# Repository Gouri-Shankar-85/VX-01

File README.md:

# VX-01 Multi-Terrain Robot

A modular multi-terrain robotic platform combining the agility of a hexapod crawler with the aerial capabilities of a multirotor drone. The system is designed for autonomous and manual navigation across land and air, powered by a distributed compute architecture using ROS 2 and ArduPilot.

---

## 🌟 Key Features

- **Hexapod Locomotion:** Real-time 18-DOF inverse kinematics (IK) executing synchronized Tripod and Wave gaits.
- **Aerial Flight:** Fully integrated drone flight (STABILIZE, GUIDED, AUTO) utilizing a MAVROS bridge.
- **Hybrid Mode Management:** Safe state machine transitioning the robot from ground crawling to aerodynamic flight postures.
- **Visual SLAM & Odometry:** RTAB-Map integration using depth camera data for 3D point cloud generation and obstacle avoidance.
- **Computer Vision:** Real-time object detection, victim identification, and terrain walkability classification using YOLOv4-tiny.
- **Mission Control Dashboard:** A sleek, React-based web UI communicating over `rosbridge_server` for live telemetry, manual teleop, and mapping visualization.

---

## 🛠️ Hardware Stack

| Component | Description |
|-----------|-------------|
| **RDK X5 (ARM64)** | High-level compute board running Ubuntu 22.04 + ROS 2 Humble (Dockerized). Handles IK, SLAM, Vision, and the Web Dashboard. |
| **Radiolink PIX6 (ArduPilot)** | Flight controller connected via USB (MAVLink). Manages aerial stabilization, IMU processing, and GPS. |
| **Pololu Maestro Mini** | Dedicated serial servo controller actuating the 18 high-torque hexapod leg servos. |
| **YDLIDAR HP60C RGBD** | Depth Camera mounted on the front chassis for perception and mapping. |
| **Benewake TFmini-S** | Downward-facing LiDAR distance sensor for precise altitude holding. |
| **Hiwonder IM10A** | External IMU for redundant odometry. |

---

## 📦 Workspace Architecture

The software is strictly modularized into distinct ROS 2 packages within the `vx01_ws/src` directory:

```
vx01_ws/src
├── vx01_bringup          # Master hardware/sim launch files and QoS relays
├── vx01_camera           # Driver for the YDLIDAR depth camera
├── vx01_control          # Locomotion meta-package (Aerial, Aquatic, Hexapod IK, Mode Manager)
├── vx01_description      # Robot URDF, Xacro kinematics, and STL 3D meshes
├── vx01_hardware         # ros2_control interfaces for the Pololu Maestro and Drone GPIOs
├── vx01_imu              # External I2C/Serial IMU drivers
├── vx01_mapping          # RTAB-Map visual SLAM integration
├── vx01_mavros_bridge    # C++ nodes bridging ArduPilot/MAVROS telemetry to custom topics
├── vx01_msgs             # Custom ROS 2 interfaces (DroneState, HexapodState, Thrust)
├── vx01_perception       # OpenCV + YOLOv4-tiny stack for victim and terrain detection
└── vx01_simulation       # Gazebo SITL physics environments
```
*(Refer to the individual `README.md` inside each package for detailed node, topic, and build instructions.)*

---

## 🚀 Quick Start Guide

This project is fully containerized. Please refer to the [VX01 Docker & Deployment Manual](VX01_Docker_Manual.md) in the root directory for complete, in-depth documentation.

### 1. Simulation on Laptop
Run the simulation stack (Gazebo + ROS 2 Bridge + Dashboard) on your computer without needing the physical hardware:

```bash
cd ~/vx-01
# Start the simulation profile containers in the background
docker compose --profile sim up -d

# Open the Gazebo simulation window from inside the container
docker exec -it vx01-sim bash
ros2 launch vx01_simulation sim.launch.py
```
Open a browser and go to `http://localhost:5173` to control the simulated robot!

### 2. Daily Code Development
To edit code and test it without affecting the real robot:

```bash
cd ~/vx-01
# Start the development container
docker compose --profile dev up -d
docker exec -it vx01-dev bash

# Once inside the container, build the workspace:
cd /vx01_ws
colcon build --symlink-install
source install/setup.bash
```
*Note: Your `~/vx-01/vx01_ws/src/` folder is mounted live into the container. Any code changes you make on your laptop instantly appear inside!*

### 3. Deploying to Real Hardware (RDK X5 / Raspberry Pi)
To update the physical robot with your latest code:

```bash
# On your laptop, trigger the ARM64 cloud build:
./build.sh build-arm-ci
# (Wait for the GitHub Action to finish building the image)

# SSH into your robot and pull the latest image:
docker pull gourishankar85/vx01-base:humble-arm64
docker compose -f ~/vx01/docker-compose.rdk.yml down
docker compose -f ~/vx01/docker-compose.rdk.yml up -d
```

### Accessing the Dashboard
Whenever the `sim` or hardware containers are running, you can access the Mission Control Dashboard:
- **Locally (Simulation):** `http://localhost:5173`
- **Real Robot:** `http://<ROBOT_IP>:5173`

---

## 🤝 Contributing
Pull requests are welcome. When adding new ROS 2 nodes, ensure they are properly integrated into the `vx01_bringup` launch files and that relevant `ros2_control` hardware parameters are updated.

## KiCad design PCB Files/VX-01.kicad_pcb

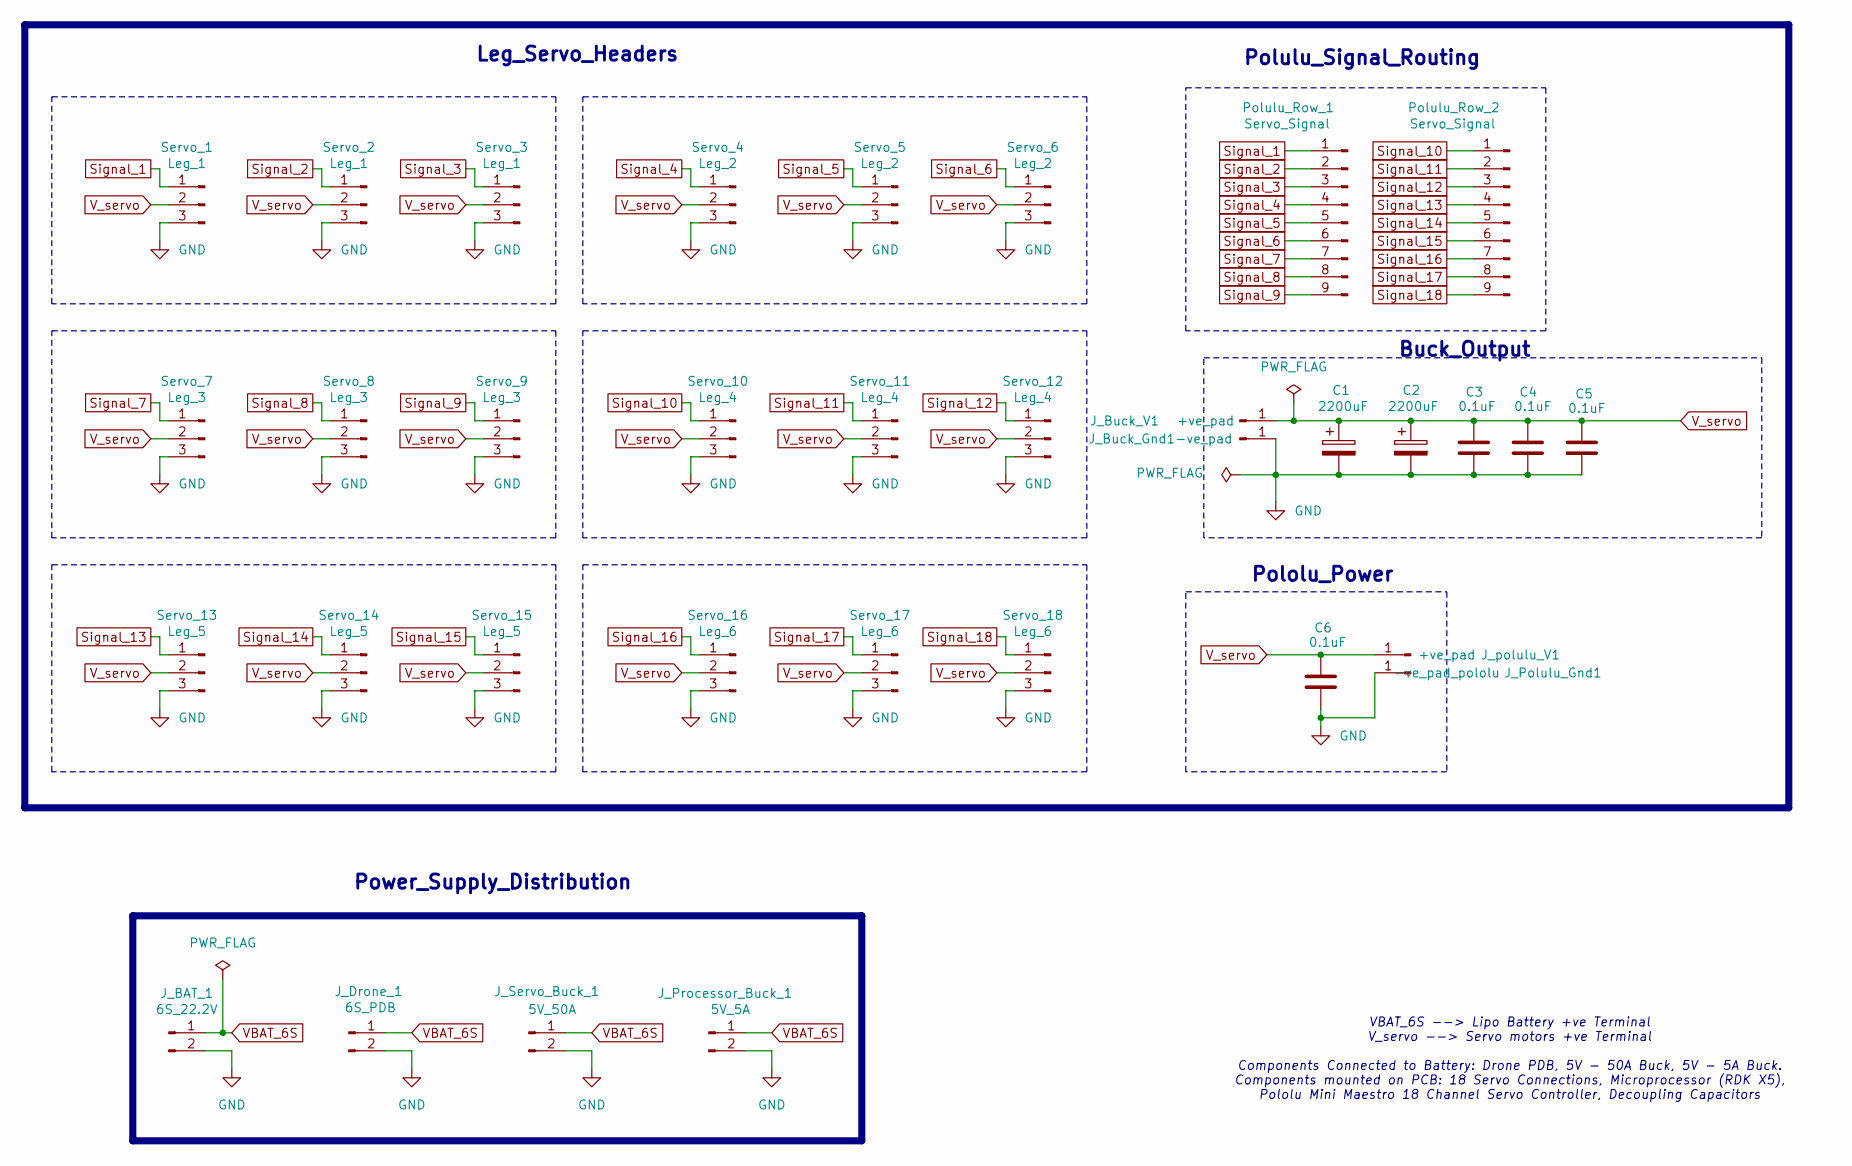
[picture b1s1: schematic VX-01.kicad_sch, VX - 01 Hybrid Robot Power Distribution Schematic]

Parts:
C1, C2: 2200uF; C_Radial_D12.5mm_H25.0mm_P5.00mm
C3, C4, C5, C6: 0.1uF; C_0805_2012Metric_Pad1.18x1.45mm_HandSolder
J_BAT_1: 6S_22.2V; XT-90F
J_Buck_Gnd1: -ve_pad; SolderWirePad_1x01_SMD_5x10mm
J_Buck_V1: +ve_pad; SolderWirePad_1x01_SMD_5x10mm
J_Drone_1: 6S_PDB; XT-90F
J_Polulu_Gnd1: -ve_pad_pololu; SolderWirePad_1x01_SMD_5x10mm
J_Processor_Buck_1: 5V_5A; AMASS_XT60-F_1x02_P7.20mm_Vertical
J_Servo_Buck_1: 5V_50A; AMASS_XT60-F_1x02_P7.20mm_Vertical
J_polulu_V1: +ve_pad; SolderWirePad_1x01_SMD_5x10mm
Polulu_Row_1, Polulu_Row_2: Servo_Signal; PinHeader_1x09_P2.54mm_Vertical
Servo_1, Servo_2, Servo_3: Leg_1; PinHeader_1x03_P2.54mm_Vertical
Servo_4, Servo_5, Servo_6: Leg_2; PinHeader_1x03_P2.54mm_Vertical
Servo_7, Servo_8, Servo_9: Leg_3; PinHeader_1x03_P2.54mm_Vertical
Servo_10, Servo_11, Servo_12: Leg_4; PinHeader_1x03_P2.54mm_Vertical
Servo_13, Servo_14, Servo_15: Leg_5; PinHeader_1x03_P2.54mm_Vertical
Servo_16, Servo_17, Servo_18: Leg_6; PinHeader_1x03_P2.54mm_Vertical

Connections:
GND: C1.2, C2.2, C3.2, C4.2, C5.2, C6.2, J_BAT_1.2, J_Buck_Gnd1.1, J_Drone_1.2, J_Polulu_Gnd1.1, J_Processor_Buck_1.2, J_Servo_Buck_1.2, Servo_1.3, Servo_2.3, Servo_3.3, Servo_4.3, Servo_5.3, Servo_6.3, Servo_7.3, Servo_8.3, Servo_9.3, Servo_10.3, Servo_11.3, Servo_12.3, Servo_13.3, Servo_14.3, Servo_15.3, Servo_16.3, Servo_17.3, Servo_18.3
Signal_1: Polulu_Row_1.1, Servo_1.1
Signal_2: Polulu_Row_1.2, Servo_2.1
Signal_3: Polulu_Row_1.3, Servo_3.1
Signal_4: Polulu_Row_1.4, Servo_4.1
Signal_5: Polulu_Row_1.5, Servo_5.1
Signal_6: Polulu_Row_1.6, Servo_6.1
Signal_7: Polulu_Row_1.7, Servo_7.1
Signal_8: Polulu_Row_1.8, Servo_8.1
Signal_9: Polulu_Row_1.9, Servo_9.1
Signal_10: Polulu_Row_2.1, Servo_10.1
Signal_11: Polulu_Row_2.2, Servo_11.1
Signal_12: Polulu_Row_2.3, Servo_12.1
Signal_13: Polulu_Row_2.4, Servo_13.1
Signal_14: Polulu_Row_2.5, Servo_14.1
Signal_15: Polulu_Row_2.6, Servo_15.1
Signal_16: Polulu_Row_2.7, Servo_16.1
Signal_17: Polulu_Row_2.8, Servo_17.1
Signal_18: Polulu_Row_2.9, Servo_18.1
VBAT_6S: J_BAT_1.1, J_Drone_1.1, J_Processor_Buck_1.1, J_Servo_Buck_1.1
V_servo: C1.1, C2.1, C3.1, C4.1, C5.1, C6.1, J_Buck_V1.1, J_polulu_V1.1, Servo_1.2, Servo_2.2, Servo_3.2, Servo_4.2, Servo_5.2, Servo_6.2, Servo_7.2, Servo_8.2, Servo_9.2, Servo_10.2, Servo_11.2, Servo_12.2, Servo_13.2, Servo_14.2, Servo_15.2, Servo_16.2, Servo_17.2, Servo_18.2

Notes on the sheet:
Leg_Servo_Headers
Pololu_Power
Polulu_Signal_Routing
Buck_Output
VBAT_6S --> Lipo Battery +ve Terminal V_servo --> Servo motors +ve Terminal Components Connected to Battery: Drone PDB, 5V - 50A Buck, 5V - 5A Buck. Components mounted on PCB: 18 Servo Connections, Microprocessor (RDK X5), Pololu Mini Maestro 18 Channel Servo Controller, Decoupling Capacitors
Power_Supply_Distribution

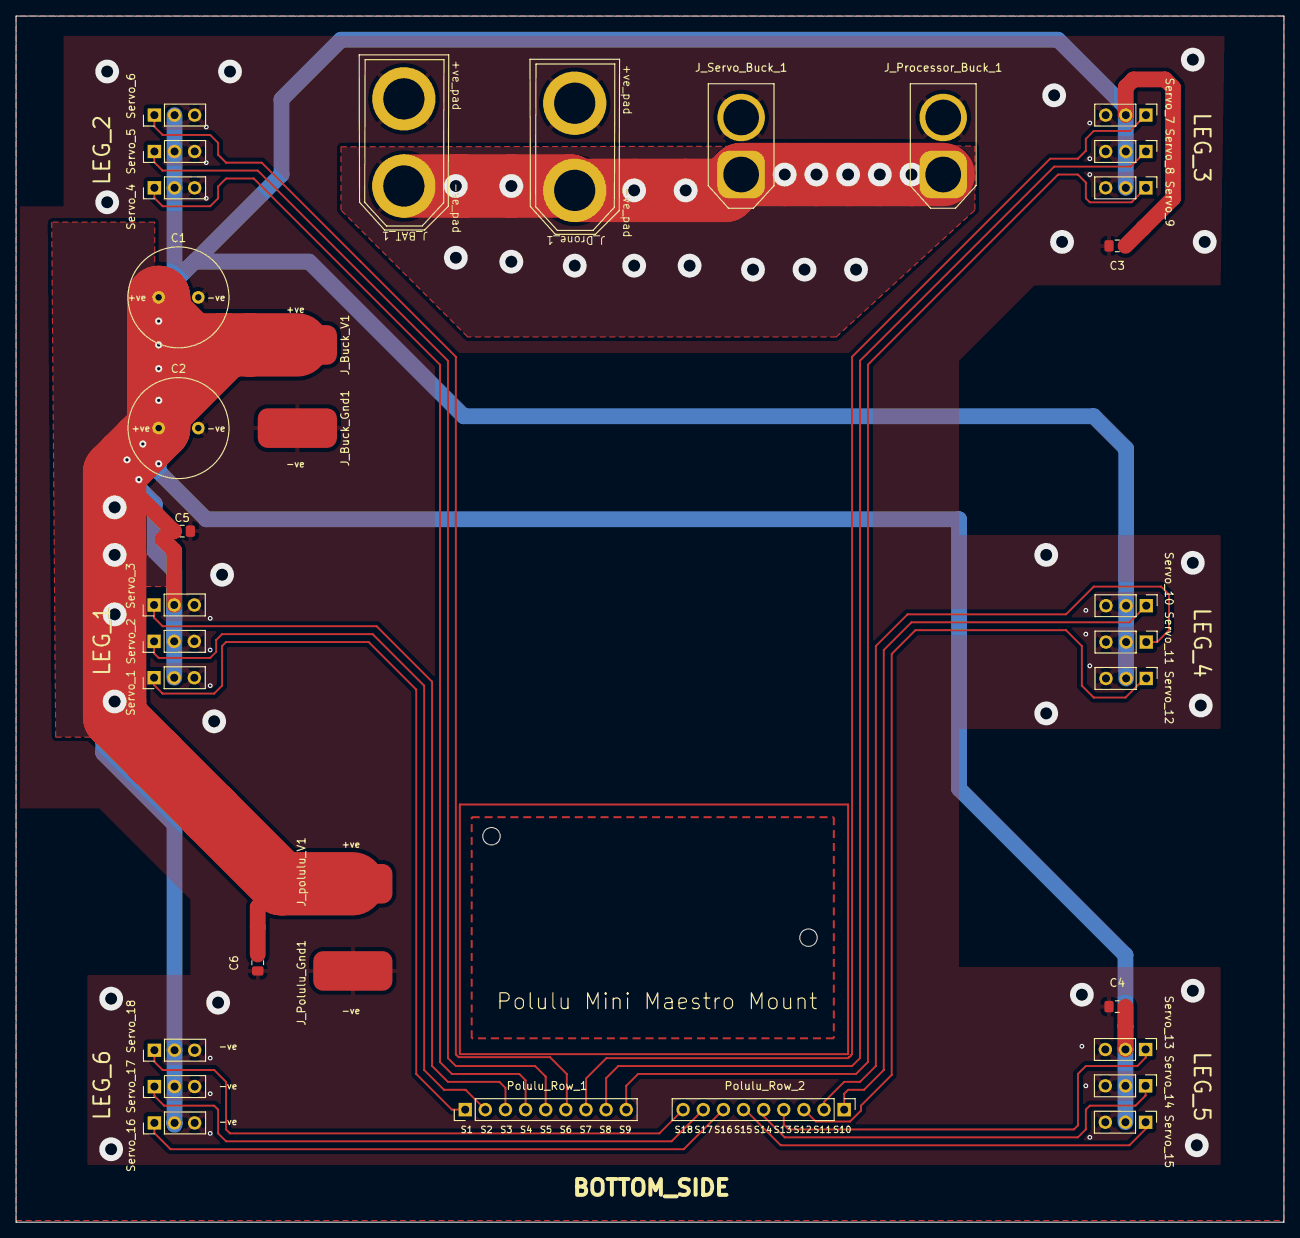
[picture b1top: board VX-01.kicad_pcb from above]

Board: 2 copper layers, 160.0 x 152.2 mm, 34 parts (0 on the bottom side), 21 nets.

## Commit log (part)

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2026-02-26 lib updated
2026-02-26 bezeir curve fixed
2026-02-26 locomotion updated
2026-02-26 to tibi
2026-02-26 hexapod walk node
2026-02-27 walk node updated
2026-03-06 camera sdk removed
2026-03-06 demo removed
2026-03-07 fix: hexapod joint limits changed
2026-03-07 walk goal script
2026-03-07 locomotion parameters
2026-03-08 feat(locomotion): add ROS2 node with tripod gait, IK-based walking, and standby pose sequencing
2026-03-08 fix: home_z set to stay within tibia limit
2026-03-08 fix(locomotion): slow step_period and add use_sim_time to unblock joint execution in Gazebo
2026-03-08 fix(locomotion): remove velocity scaling so open-loop gait actually translates feet
2026-03-08 test(ik): theta_3 sign chnaged
2026-03-08 fix: Bezier swing arc + full drag sweep for all 6 legs
2026-03-08 fix: projects the stride onto each leg's local frame using the mounting angle alpha
2026-03-08 fix(description(: initial pose for hexapod sim changed
2026-03-08 fix(locomotion): correct forward walk IK by reducing home_x and fixing body_radius double-count in updateLeg
2026-03-08 test: gait_x value passed to ik_x
2026-03-08 test: local_y changed to cos to fix the sideways walk
2026-03-08 test: ik_y changed to have a leg frame calculation
2026-03-08 fix(gait): remove duplicate global_t declaration in drag phase
2026-03-08 feat(body): add BodyKinematics and BodyTranslation modules; wire updateLeg through O-frame transform per reference
2026-03-08 fix(locomotion): pass (home_x - body_radius) as O-frame body_x into bodyToLegFrame to fix diagonal leg IK failures
2026-03-08 fix(config): reduce step_length to 50 to fit diagonal leg IK reach with home_x=222.8
2026-03-08 locomotion fixed
2026-03-09 home_x changed
2026-03-09 fix: add home_z offset to gait_z in updateLeg
2026-03-09 fix: reduce home_x and step_length to eliminate stretched leg posture
2026-03-09 test:theta_3 sig reverted back
2026-03-09 fix: tune yaml for IK reachability
2026-03-09 fix: project stride offset into leg-local frame in updateLeg, tune yaml for IK reachability
2026-03-10 feat(vx01_msgs): add 8 custom msg types for victim detection, terrain, mission, and robot status
2026-03-10 fix:mount the workspace into the container.
2026-03-11 add(perception): perception nodes - victim detector, terrain classifier and mission nodes
2026-03-13 fix: hexapod hw controller and launch file update
2026-03-13 Ignore core dumps and vx01_camera
2026-03-13 local changes before pull
2026-03-13 fix(launch): correct parameter order and types in hw launch file
2026-03-13 fix(urdf): pass serial_port and baud_rate as xacro args instead of hardcoding
2026-03-13 update : servo mapping coxa reversed
2026-03-14 feat(servo): add software interpolation for smooth joint motion
2026-03-14 fix(locomotion): correct IK femur sign, fix JTC flooding, fix gait block-rate sending
2026-03-14 fix: locomotion parameters updated
2026-03-14 fix: restore single-point sendLegTrajectory overload for standby pose, suppress unused S warning
2026-03-14 fix: correct tripod gait to true 50/50 duty cycle, remove all-stance block 5
2026-03-19 fix: correct tripod stride direction, separate swing/stance trajectory dispatch
2026-03-19 fix: use full bezier bx/by/bz for swing, scale*T/2 for drag Y
2026-03-19 fix: ik 'r2' eqn corrected
2026-03-20 fix: validateWorkspace use Y-sweep check; increase step_height for visible lift
2026-03-20 fix(locomotion): tripod gait sync, drag leg hold, and stride length
2026-03-21 fix: fire trajectories only at group-start blocks 0/3; full 3-block swing+drag per trigger
2026-03-21 fix: separate swing/drag send loops to prevent mid-motion interruption; step_height=70
2026-03-21 update: femur standy pose to -1.2
2026-03-21 fix: decouple theta1 coxa sweep from theta2/theta3 Z lift in sampleSwingAtGlobalT
2026-03-21 fix: use stance_femur/tibia directly in swing; no IK coupling; femur lifts correctly
2026-03-22 feat: add turn-in-place node with CCW/CW direction param
2026-03-22 fix: hexapod_fw_walk_node updated with correct lib name
2026-03-22 fix: add __main__ guard to victim_detector_node
2026-03-22 fix: explicit bool casts and NaN guard in terrain_classifier_node
2026-03-22 fix: remove viz, add static TF
2026-03-22 feat: lifecycle walk/turn nodes with autonomous victim approach node
2026-03-23 docker: dockerfile base libuvc to uvc
2026-03-23 updated dockerfile base
2026-03-23 build.sh updted to try 3 times to build he image
2026-03-24 git commit -m "fix: dynamic rosbridge URL from window.location, fix dockerignore"
2026-03-24 regenerate package-lock.json with roslib and socket.io deps
2026-03-24 fix(vx01_msgs): add rosidl runtime export for proper package discovery
2026-03-25 locomotion: fixed for standalone testing of hexapod
2026-03-25 revert(locomotion): remove lifecycle nodes, restore original plain Node walk/turn
2026-03-25 update: removed gpio group from dockerfile.base
2026-03-26 fix: added a use sim time argument to forward walk launch file
2026-03-26 test: increased the step height and step length
2026-03-26 locmotion: cmakelist updated
2026-03-26 Fix gait_config.yaml: correct leg_joint_names format to map (0-5 keys)
2026-03-27 fix(locomotion): derive home pose from xacro FK and raise controller trajectory tolerance
2026-04-05 feat: add vx01_msgs dependency to package.xml
2026-04-05 feat: enhance dashboard with real-time telemetry, robot status monitoring, and expanded manual control capabilities
2026-04-05 feat: implement ArduPilot SITL integration, hybrid mode manager, and aerial controller nodes
2026-04-05 feat: enable IMU and sensor plugins with ogre2 render engine in empty_world.sdf
2026-04-05 fix: update IMU topic configuration and sensor name reference for Gazebo bridge compatibility
2026-04-05 fix: update MAVProxy and MAVROS connection protocol from TCP to UDP for improved telemetry stability
2026-04-05 refactor: update ArduPilot simulation arguments and switch MAVROS connection to TCP port 5760
2026-04-05 feat: enable use_sim_time in mavros launch parameters
2026-04-05 feat: add velocity command and state interfaces for four propeller joints to ros2_control configuration
2026-04-05 feat: initialize backend node_modules and update robot URDF configuration
2026-04-05 feat: integrate RTAB-Map for SLAM and update simulation launch configurations to support use_sim_time
2026-04-05 feat: add MAVROS drone control support, telemetry stream configuration, and force-arming capabilities
2026-04-05 feat: add ArduPilot simulation bypass parameters, implement cycle-based trajectory synchronization in locomotion, and tune RTAB-Map simulation settings.
2026-04-05 refactor: optimize RTAB-Map odometry parameters and update force-arm sequence to STABILIZE mode for improved reliability
2026-04-06 refactor: optimize IK calculations and adjust gait parameters for improved workspace stability
2026-04-06 fix: replace invalid --out argument with --serial0 for ArduPilot SITL MAVLink output
2026-04-08 refactor: switch MAVROS connection from TCP to UDP for improved simulation stability
2026-04-08 refactor: implement leg-to-body frame transformations, update gait parameters for tripod stability, and correct ArduPilot plugin configuration.
2026-04-08 feat: add rosbridge_server to launch configuration and fix ArduPilotPlugin library path in URDF
2026-04-08 chore: update ArduPilot serial port to 14551 and simplify MAVROS fcu_url configuration
2026-04-08 fix: update MAVROS fcu_url configuration and remove redundant comments in hybrid simulation launch file
2026-04-08 fix: swap MAVROS fcu_url ports to correct UDP communication direction
2026-04-08 chore: update ArduPilot SITL model and switch MAVROS connection to TCP
2026-04-08 feat: load ArduPilot default parameters and remove redundant MAVROS frame configuration services
2026-04-08 feat: add additional periodic arming attempts to hybrid simulation launch file
2026-04-08 refactor: update drone control to use TwistStamped messages and clean up UI logging and labels
2026-04-08 feat: add ardupilot_sim_bypass.param to SITL launch configuration
2026-04-09 fix: update ROS message type and include header timestamps in takeoff command velocity publisher
2026-04-09 feat: enable use_sim_time for aerial_controller node in hybrid simulation launch
2026-04-09 fix: update ArduPilotPlugin name to match library expectations
2026-04-21 refactor: update hexapod kinematics, gait trajectory interpolation, and default configuration parameters while adding a walk test script.
2026-04-21 refactor: update kinematics, gait parameters, and add Bézier trajectory support for improved locomotion stability
2026-04-21 refactor: clean up backend logs and remove unused simulation shutdown logic
2026-04-24 refactor: simplify hexapod configuration comments and remove deprecated walk test script
2026-04-24 refactor: replace C++ aerial control node with Python-based implementation using rclpy and MAVROS
2026-04-24 fix: update ArduPilotPlugin namespace to ignition::gazebo::systems
2026-04-24 fix: adjust MAVROS parameter timeouts, reorder ArduPilot launch arguments, and update bypass parameters for simulation stability
2026-04-24 chore: configure ArduPilot RC and motor parameters and increase URDF motor multipliers
2026-04-24 feat: add robotNamespace to multicopter motor model plugins in URDF
2026-04-24 fix: increase motor multiplier values in URDF to correct propulsion output scale
2026-04-24 chore: update base inertia properties and reconfigure propeller servo limits
2026-04-24 chore: adjust simulation spawn height and reset gazebo coordinate transformation parameters
2026-04-24 chore: update propeller controller multiplier and p_gain values in URDF
2026-04-24 chore: update ArduPilot serial parameters and tune motor controller gains in URDF
2026-04-25 feat: enable orientation output in IMU sensor configuration
2026-04-25 refactor: update motor control parameters and streamline flight mode transition to GUIDED for takeoff
2026-04-25 chore: update ArduPilot simulation parameters for rate controller and filtering settings
2026-04-26 chore: normalize arm joint orientations and update ArduPilot PID tuning parameters
2026-04-26 refactor: update friction coefficients in simulation and remove IMU bias noise parameters
2026-04-26 chore: increase p_gain from 0.5 to 5.0 for velocity servos in URDF description
2026-04-26 chore: tune MAVROS connection timeouts and update motor control parameters in URDF
2026-04-27 feat: add teleop launch buttons and manual control toggles to hexapod and drone dashboards
2026-04-27 Fix: Add camera SDK path to LD_LIBRARY_PATH
2026-04-28 Fix: Pin Maestro symlink to Command Port (Interface 0)
2026-04-28 chore: update gait parameters and apply tibia joint offset for high-precision movement
2026-04-28 chore: adjust hexapod gait parameters for improved reachability and stability
2026-04-29 chore: adjust home Z-height, increase stand duration, and apply joint offset corrections to locomotion kinematics
2026-04-29 feat: implement dynamic home coordinate calculation and update locomotion gait parameters
2026-04-29 chore: update hexapod gait parameters and home position for increased stability
2026-04-29 chore: update step_period in hexapod configuration to 2.0 seconds for optimized gait cycle
2026-04-29 chore: update stand-pose joint commands and home position for improved walking IK alignment
2026-05-04 feat: add drone attitude visualization and real-time telemetry metrics to dashboard
2026-05-05 build: add host network driver option to buildx builder creation
2026-05-11 feat: update camera resolution settings, fix hexapod angle calculation, and add MAVROS distance sensor configuration
2026-05-11 Fix typo in hexapod_node.py
2026-05-11 Fix undefined function crash in dashboard and satisfy Pixhawk RC arming checks
2026-05-11 docs: Add hero image to main README
2026-05-12 docs: Generate clean tree-based READMEs matching the original camera documentation format
2026-05-12 docs: Update hardware specs and align quickstart instructions with Docker manual
